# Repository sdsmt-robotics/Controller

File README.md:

# ARCHIVED. USE GITLAB.

# Controller
Repo is used to document all the iterations for the controller

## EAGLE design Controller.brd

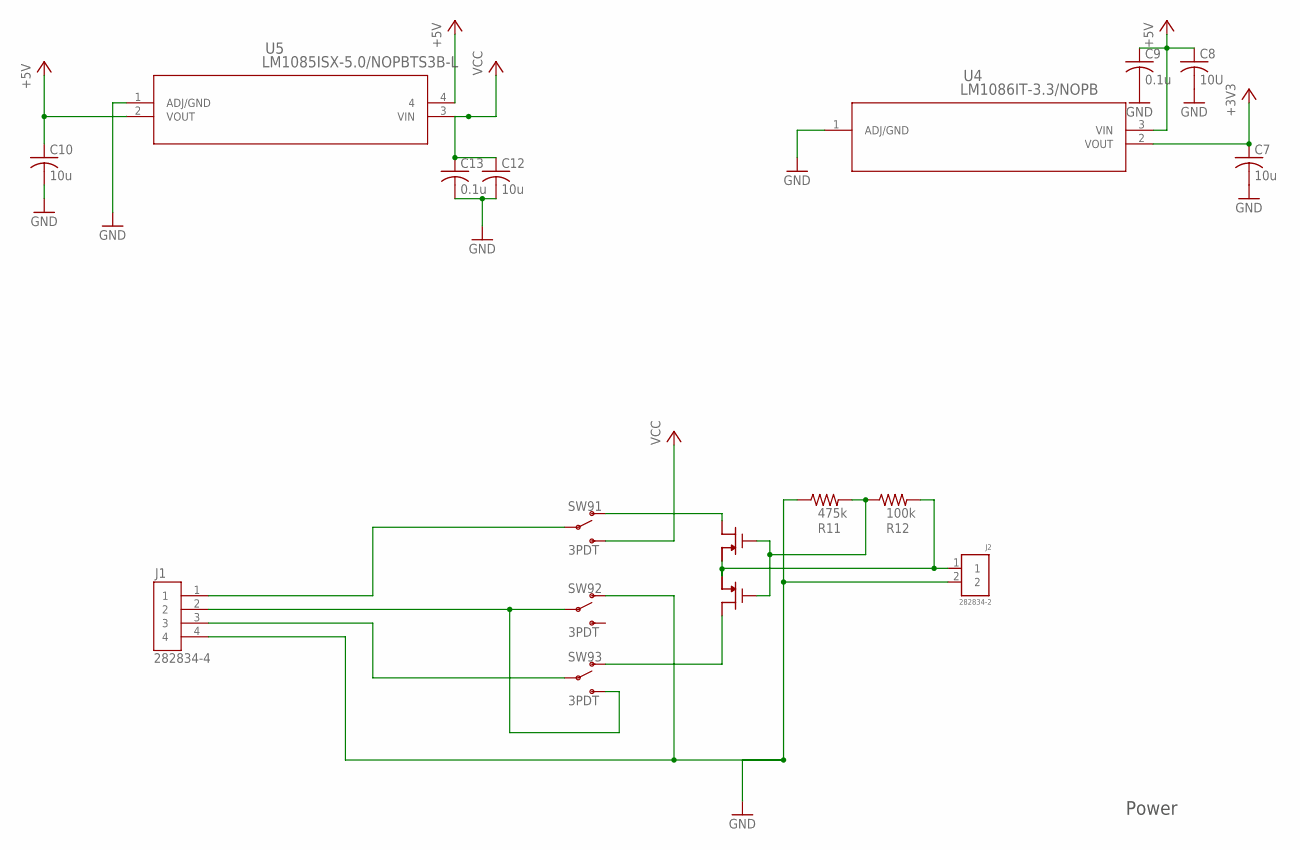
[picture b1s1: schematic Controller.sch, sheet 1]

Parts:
C7, C10, C12: 10u; C1206
C8: 10U; C1206
C9, C13: 0.1u; C1206
J1: 282834-4; HDRV4W85P254_4X1_1062X650X1000
J2: 282834-2; CONN_282834-2
R11: 475k; R1206
R12: 100k; R1206
SW9: 3PDT
U4: LM1086IT-3.3/NOPB; T03B
U5: LM1085ISX-5.0/NOPBTS3B-L; TS3B-L
U6: SSM6P40TULFCT-ND; SMD6

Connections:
+3V3: C7.1, U4.2 (VOUT); also elsewhere on the board
+5V: C8.1, C9.1, C10.1, U4.3 (VIN), U5.2 (VOUT), U5.4; also elsewhere on the board
GND: C7.2, C8.2, C9.2, C10.2, C12.2, C13.2, J1.4, J2.2, R11.1, SW9.T21 (O), U4.1 (ADJ/GND), U5.1 (ADJ/GND); also elsewhere on the board
unnamed: J1.1, SW9.P1
unnamed: J1.2, SW9.P2, SW9.T32 (S)
unnamed: J1.3, SW9.P3
unnamed: SW9.T31 (O), U6.P$3 (D)
unnamed: J2.1, R12.2, U6.P$1 (S), U6.P$4 (S)
unnamed: SW9.T11 (O), U6.P$6 (D)
unnamed: R11.2, R12.1, U6.P$2 (G), U6.P$5 (G)
VCC: C12.1, C13.1, SW9.T12 (S), U5.3 (VIN)

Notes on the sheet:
Power

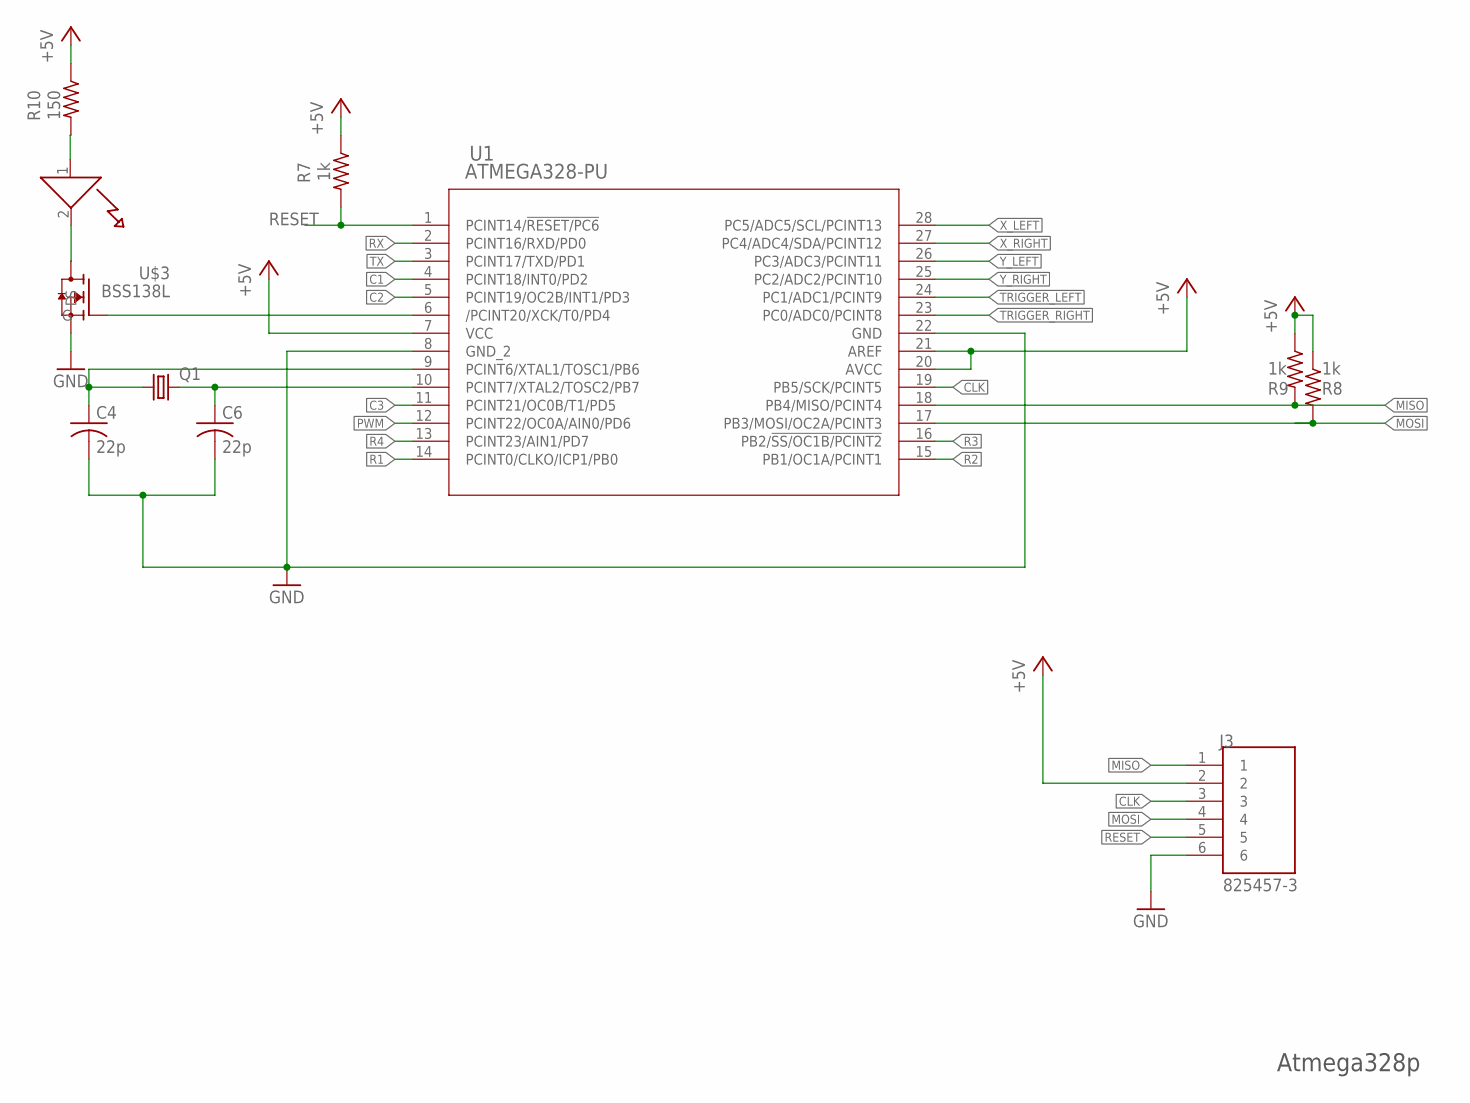
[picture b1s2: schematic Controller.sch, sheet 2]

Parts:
C4, C6: 22p; C1206
J3: 825457-3; TE_825457-3
Q1: CRYSTALHC49S; HC49/S
R7, R8, R9: 1k; R1206
R10: 150; R1206
U1: ATMEGA328-PU; 28P3
U$2: LED; R1206W
U$3: BSS138L

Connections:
+5V: J3.2, R7.1, R8.1, R9.1, R10.1, U1.7 (VCC), U1.20 (AVCC), U1.21 (AREF); also elsewhere on the board
C1: U1.4 (PCINT18/INT0/PD2); also elsewhere on the board
C2: U1.5 (PCINT19/OC2B/INT1/PD3); also elsewhere on the board
C3: U1.11 (PCINT21/OC0B/T1/PD5); also elsewhere on the board
CLK: J3.3, U1.19 (PB5/SCK/PCINT5)
GND: C4.2, C6.2, J3.6, U1.8 (GND_2), U1.22 (GND), U$3.S; also elsewhere on the board
MISO: J3.1, R9.2, U1.18 (PB4/MISO/PCINT4)
MOSI: J3.4, R8.2, U1.17 (PB3/MOSI/OC2A/PCINT3)
unnamed: C4.1, Q1.1, U1.9 (PCINT6/XTAL1/TOSC1/PB6)
unnamed: C6.1, Q1.2, U1.10 (PCINT7/XTAL2/TOSC2/PB7)
unnamed: U1.6 (/PCINT20/XCK/T0/PD4), U$3.G
unnamed: U$2.2, U$3.D
unnamed: R10.2, U$2.1
PWM: U1.12 (PCINT22/OC0A/AIN0/PD6)
R1: U1.14 (PCINT0/CLKO/ICP1/PB0); also elsewhere on the board
R2: U1.15 (PB1/OC1A/PCINT1); also elsewhere on the board
R3: U1.16 (PB2/!SS/OC1B/PCINT2); also elsewhere on the board
R4: U1.13 (PCINT23/AIN1/PD7); also elsewhere on the board
RESET: J3.5, R7.2, U1.1 (PCINT14/!RESET/PC6)
RX: U1.2 (PCINT16/RXD/PD0); also elsewhere on the board
TRIGGER_LEFT: U1.24 (PC1/ADC1/PCINT9); also elsewhere on the board
TRIGGER_RIGHT: U1.23 (PC0/ADC0/PCINT8); also elsewhere on the board
TX: U1.3 (PCINT17/TXD/PD1); also elsewhere on the board
X_LEFT: U1.28 (PC5/ADC5/SCL/PCINT13); also elsewhere on the board
X_RIGHT: U1.27 (PC4/ADC4/SDA/PCINT12); also elsewhere on the board
Y_LEFT: U1.26 (PC3/ADC3/PCINT11); also elsewhere on the board
Y_RIGHT: U1.25 (PC2/ADC2/PCINT10); also elsewhere on the board

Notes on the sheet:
Atmega328p

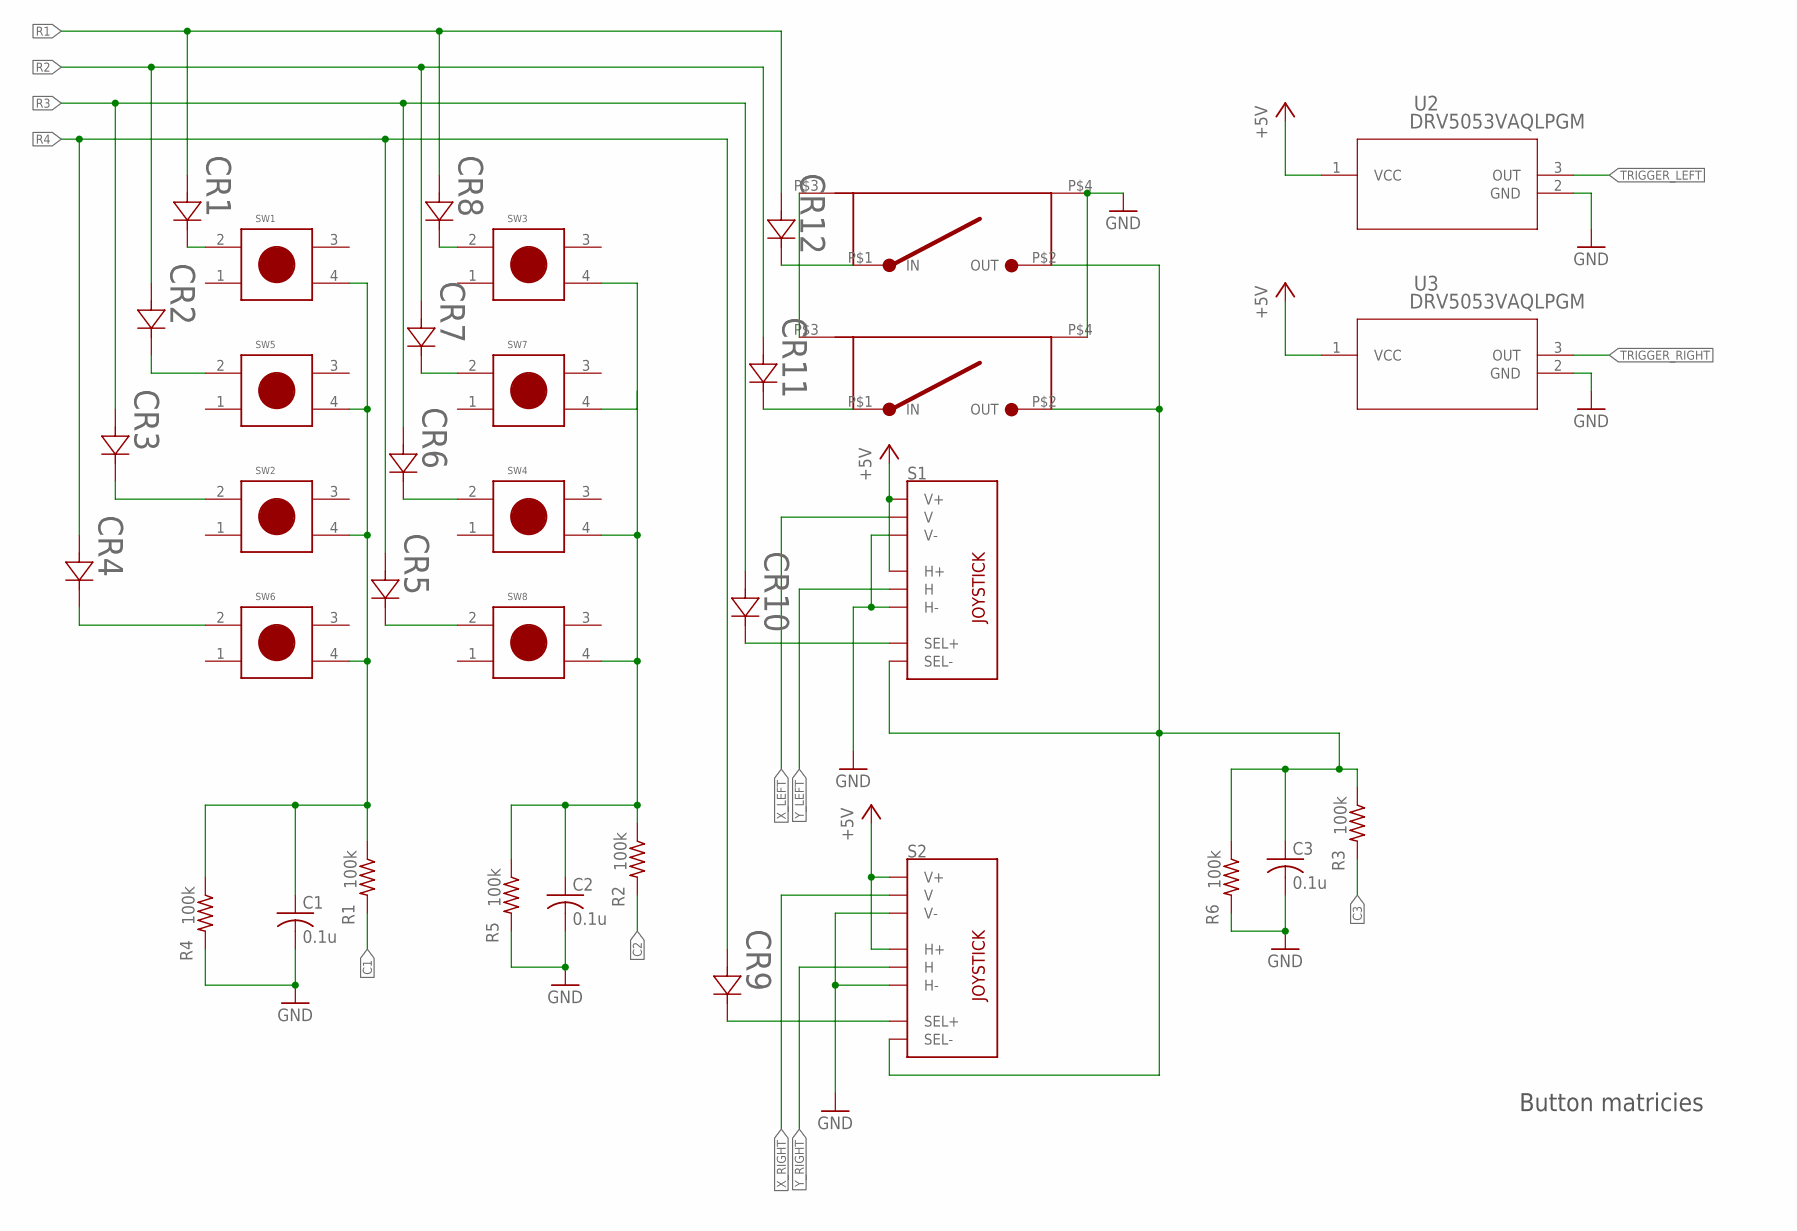
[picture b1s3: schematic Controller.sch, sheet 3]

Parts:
C1, C2, C3: 0.1u; C1206
CR1, CR2, CR3, CR4, CR5, CR6, CR7, CR8, CR9, CR10, CR11, CR12: MSS1P6-M3/89ADIODE_MSP3V3-M; DIODE_MSP3V3-M
R1, R2, R3, R4, R5, R6: 100k; R1206
S1, S2: THUMBPOINTER-RKJXV1224005
SW1, SW2, SW3, SW4, SW5, SW6, SW7, SW8: MULTICOLOR_BUTTON; PRT-14460
U2, U3: DRV5053VAQLPGM; LPG3
U$4, U$6: BUMPER_BUMPER

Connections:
$NC1: C1.1, R1.1, R4.1, SW1.4, SW2.4, SW5.4, SW6.4
+5V: S1.H1 (H+), S1.V1 (V+), S2.H1 (H+), S2.V1 (V+), U2.1 (VCC), U3.1 (VCC); also elsewhere on the board
C1: R1.2; also elsewhere on the board
C2: R2.2; also elsewhere on the board
C3: R3.2; also elsewhere on the board
GND: C1.2, C2.2, C3.2, R4.2, R5.2, R6.2, S1.H3 (H-), S1.V3 (V-), S2.H3 (H-), S2.V3 (V-), U2.2 (GND), U3.2 (GND), U$4.P$4 (GROUND), U$6.P$4 (GROUND); also elsewhere on the board
unnamed: CR4.1, SW6.2
unnamed: U$4.P$3 (GROUND1), U$6.P$3 (GROUND1)
unnamed: CR3.1, SW2.2
unnamed: CR2.1, SW5.2
unnamed: CR1.1, SW1.2
unnamed: CR7.1, SW7.2
unnamed: CR6.1, SW4.2
unnamed: CR5.1, SW8.2
unnamed: CR12.1, U$4.P$1 (IN)
unnamed: CR8.1, SW3.2
unnamed: CR11.1, U$6.P$1 (IN)
unnamed: CR10.1, S1.B1A (SEL+)
unnamed: CR9.1, S2.B1A (SEL+)
N$C2: C2.1, R2.1, R5.1, SW3.4, SW4.4, SW7.4, SW8.4
N$C3: C3.1, R3.1, R6.1, S1.B2A (SEL-), S2.B2A (SEL-), U$4.P$2 (OUT), U$6.P$2 (OUT)
R1: CR1.2, CR8.2, CR12.2; also elsewhere on the board
R2: CR2.2, CR7.2, CR11.2; also elsewhere on the board
R3: CR3.2, CR6.2, CR10.2; also elsewhere on the board
R4: CR4.2, CR5.2, CR9.2; also elsewhere on the board
TRIGGER_LEFT: U2.3 (OUT); also elsewhere on the board
TRIGGER_RIGHT: U3.3 (OUT); also elsewhere on the board
X_LEFT: S1.V2 (V); also elsewhere on the board
X_RIGHT: S2.V2 (V); also elsewhere on the board
Y_LEFT: S1.H2 (H); also elsewhere on the board
Y_RIGHT: S2.H2 (H); also elsewhere on the board

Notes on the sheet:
Button matricies

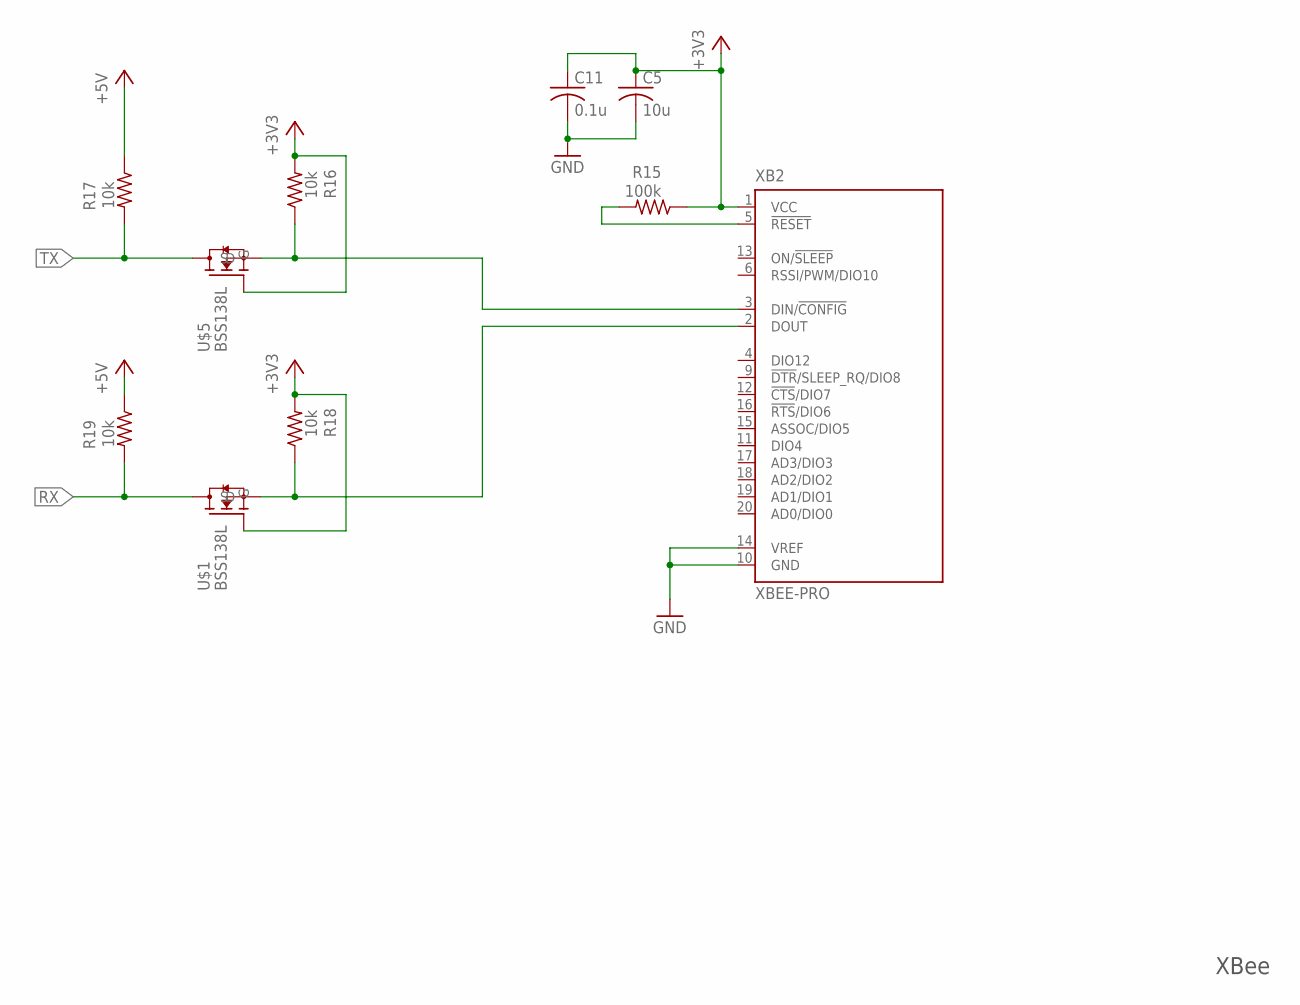
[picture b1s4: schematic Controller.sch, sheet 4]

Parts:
C5: 10u; C1206
C11: 0.1u; C1206
R15: 100k; R1206
R16, R17, R18, R19: 10k; R1206
U$1, U$5: BSS138L
XB2: XBEE-PRO

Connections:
+3V3: C5.1, C11.1, R15.1, R16.2, R18.2, U$1.G, U$5.G, XB2.1 (VCC); also elsewhere on the board
+5V: R17.1, R19.1; also elsewhere on the board
GND: C5.2, C11.2, XB2.10 (GND), XB2.14 (VREF); also elsewhere on the board
unnamed: R15.2, XB2.5 (!RESET)
unnamed: R16.1, U$5.S, XB2.3 (DIN/!CONFIG)
unnamed: R18.1, U$1.S, XB2.2 (DOUT)
RX: R19.2, U$1.D; also elsewhere on the board
TX: R17.2, U$5.D; also elsewhere on the board

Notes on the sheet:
XBee

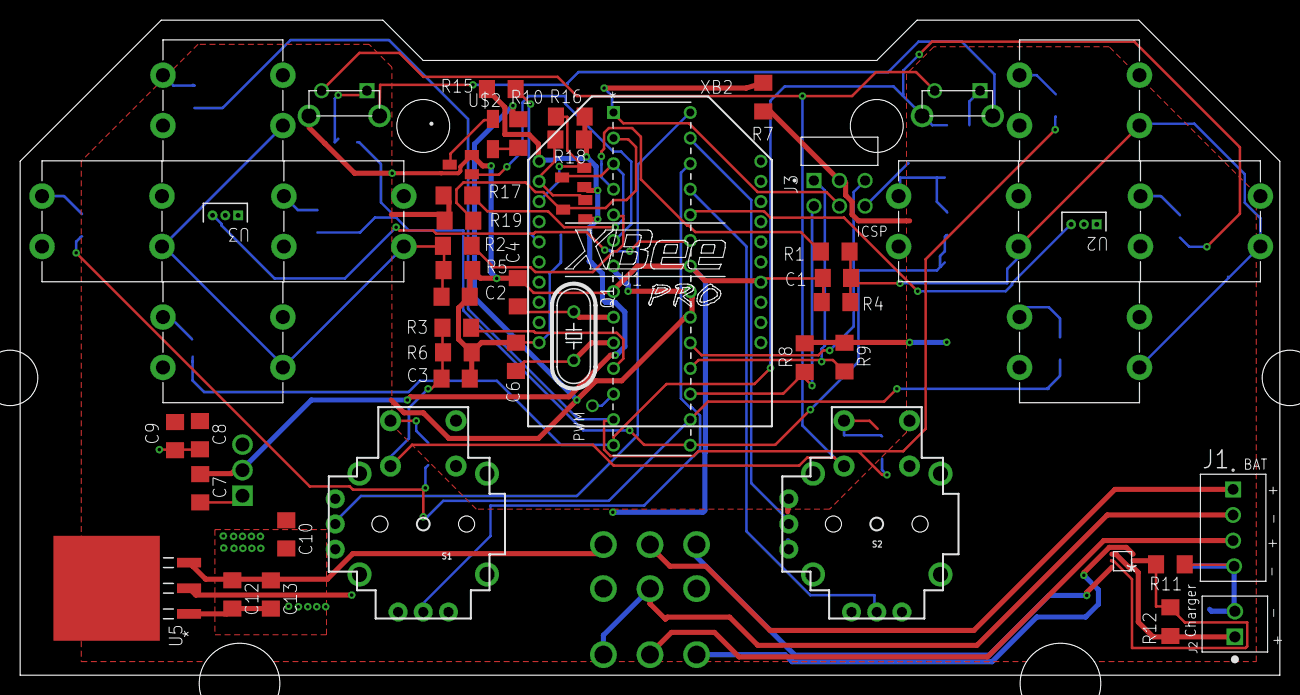
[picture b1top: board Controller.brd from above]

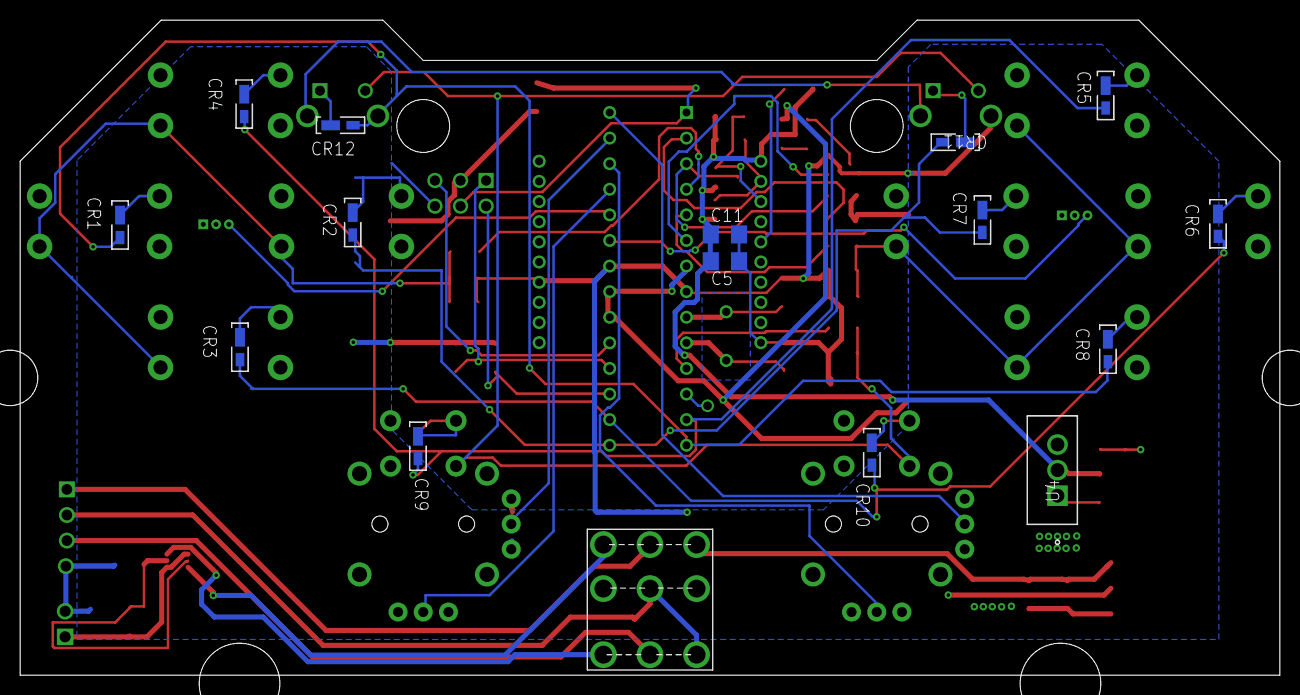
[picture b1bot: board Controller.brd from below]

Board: 2 copper layers, 125.0 x 65.0 mm, 70 parts (16 on the bottom side), 54 nets.

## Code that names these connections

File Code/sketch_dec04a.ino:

void setup() {
  // put your setup code here, to run once:
  DDRD |= (1<<PD2)|(1<<PD3)|(1<<PD4)|(1<<PD5)|(1<<PD7); // Set pins as output
  DDRB |= (1<<PB0)|(1<<PB1)|(PB2); // Set pins as output

  Serial.begin(9600);

}

void loop() {
  // put your main code here, to run repeatedly

  PORTD |= (1<<PD4); // Turn on LED
  
  while(1) // Redundant loop to by-pass Arduino overhead and increase runtime
  {
    uint16_t message_frame[10]={};
    char row_flag = 0x00; //Setup flags for what row is currently being toggled
    uint16_t *col_flag = 0x01; // and what col button might be pressed

    setframe(message_frame,row_flag++,*col_flag);
    
   // "x" in the following comments is the effective Arduino pin that's mapped to appropriate pin 
   // on the chip. Lookup Arduino pinout : https://www.circuito.io/blog/arduino-uno-pinout/
   // Notice in the picture how pin 6 on the chip is actually digital pin 4 on the arduino and is BIT
   // 4 in the D register (PD4)

  
   
    PORTB |= (1<<PB0); // digitalWrite(x,HIGH) -> Use PORTX when writing to registers, PINX when reading and DDRX when setting the pinMode
    col_flag = CheckKeyPress(); // Check for key presses
    PORTB &= ~(1<<PB0); // digitalWrite(x,LOW)
    setframe(message_frame,row_flag++,*col_flag);

    
    PORTB |= (1<<PB1);
    col_flag = CheckKeyPress();
    PORTB &= ~(1<<PB1);
    setframe(message_frame,row_flag++,*col_flag);

    PORTB |= (1<<PB2);
    col_flag = CheckKeyPress();
    PORTB &= ~(1<<PB2);
    setframe(message_frame,row_flag++,*col_flag);


    PORTD |= (1<<PD7);
    col_flag = CheckKeyPress();
    PORTB &= ~(1<<PD7);  
    setframe(message_frame,row_flag++,*col_flag);

    
    col_flag = analogRead(A0);
    setframe(message_frame,row_flag++,*col_flag);


    col_flag = analogRead(A1);
    setframe(message_frame,row_flag++,*col_flag);

    col_flag = analogRead(A2);
    setframe(message_frame,row_flag++,*col_flag);

    col_flag = analogRead(A3);
    setframe(message_frame,row_flag++,*col_flag);

    col_flag = analogRead(A4);
    setframe(message_frame,row_flag++,*col_flag);


    col_flag = analogRead(A5);
    setframe(message_frame,row_flag++,*col_flag);

    col_flag = 0x04;
    setframe(message_frame,row_flag,*col_flag);

    sendframe(message_frame);
 
  }
}

char CheckKeyPress(){
  char dreg = PIND; // Read the whole input register -> registers are 8 bit. No point in using int (32 bits). Can also use uint_8t
  if(dreg & (1<<PD2)) // If the PD2 bit in the register is set, return 1
    return 0x01;
  if(dreg & (1<<PD3))
    return 0x02;
  if(dreg & (1<<PD5))
    return 0x03;
} 

void setframe(uint16_t frame[], char index, uint16_t &col_flag)
{
    frame[index] = (col_flag);  

    col_flag = 0x00; 
}

void sendframe(uint16_t message_frame[])
{
  char i=0;
  do
  {
    Serial.write(message_frame[i]);
    delay(10);                            //UART is quirky. Can't be sending stuff too fast.
    Serial.write(message_frame[i]>>8); 
    delay(10);

  }
  while(message_frame[i++] != 0x04);

}

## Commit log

2019-09-14 Added buttons and a switch
2019-09-15 Redid debounce filter and added unity gain buffer. Added Xbee and logic level shifter for RX and TX
2019-09-15 Added 16MHz oscillator for Atmega328p
2019-09-15 Fixed connection error in Low Pass filter
2019-10-05 Update Controller.lbr
    Made a couple of changes to the board outline. Add zeners to the each button
2019-10-11 Added more holes, did some routing added 3D models
2019-10-11 MORE ROUTING!!
2019-10-12 Routing
    Routed most of the board. Need to add power components and Zeners
2019-10-19 Changes
    Added more 3D models. Changed to a ATMega2560
2019-10-20 Added Charlieplexed button matrix
    Will now have to turn on PORTB bits 1:3
2019-10-20 Added Hall effect sensors
2019-10-21 Redoing the board
2019-10-24 Added Board
2019-10-24 added 5V regulator
    Still need to add BMS circuitry and switch
2019-10-28 rerouted so we only have 2 layers, added PWM pin
    Need to add battery switch,indicator Vbat pins
2019-11-01 Added switch and LED
2019-11-02 finished?
2019-11-02 Added a License
2019-11-02 Added coherent BOM
2019-11-03 Added diodes and made traces 10 mills
2019-11-03 Minor Changes and added Gerber
2019-11-04 Updated trace width for power
    All Power traces (VCC, +3V3 and 5V) are rated for 1.5A. All other traces are rated for 0.8A
2019-11-04 Added Gerbers
2019-11-04 Added Sam's holes
2019-11-04 Read Desc.
    * Moved Bumpers 3mm lower
    * changed TO diodes to SMD
    * Chnaged BOM to shorter actuator buttons
2019-11-21 Fixed overlap and deleted some stubs
2019-12-09 Finished code? Needs to be tested
2020-01-13 Fixed pin toggeling
    Had to NOT some bits to set the pin LOW
2020-01-18 Tested
2020-02-02 Update sketch_dec04a.ino
    Mostly working controller code. Still have to fix recieving more than one button press when only pressed once. Must also make sure hall effect sensors work.
2020-02-29 Debounced buttons
    Hopefully, it's done and I don't need to adjust any delays
2020-03-01 FIxed
    Have Sam check
2020-03-13 Fix formatting in README
2020-03-13 Add communications code and documentation
2020-03-14 Fix missing joystick button in receive demo code
2020-03-14 Add code for rev3 of the controller
2020-03-15 Improve data transmission and add some functions to clean up analog values
    * Increased xbee baudrate to 115200. Nothing has caught on fire yet...
    * Split full sends into two halves so we are less likely to overflow the serial buffer.
    * Added a joystick deadzone function to the receive code
    * Changed over to floats for analog values. Performance doesn't take that much of a hit, and it is much more usable.
    * Added some scaling to analog values for rev3.
    * Added some documentation for the rev3 code.
2020-03-16 Add (mostly) working rev2 code
2020-03-17 Update documentation to add rev2 notes
2020-03-17 Add button debouncing to rev2 code
2020-08-26 Add changes to example receive code
2020-12-31 Remove debugging stuff
2022-06-14 Addimg readme
2022-06-14 Updating README
2022-06-14 Test commit
2022-08-19 Adding new block diagram
2022-08-28 Updating Files
2022-08-28 Adding CubeMX config file and generated code
2022-08-31 Updating for 3v3 operation
2022-08-31 Adding power dissipation notes. Removing WS2821B since they won't work with a 3v3 supply
2022-08-31 updating label directions
2022-09-01 Added buzz and vibe, moved SPI, added 2 LEDs
2022-09-01 Updating sheet template
2022-09-01 added switch
2022-09-02 Added Xbee libs and bus aliases
2022-09-02 Updating title block fields and adding pdf schematic
2022-09-02 Adding Block svg
2022-09-07 Adding pull ups on I2C lines
2022-09-25 Fixing USB pins and added SPI_CS
2022-09-25 Adding some device footprints and MPN
2022-10-15 No clue what changed
2022-10-21 Removed unnecessary FETs
2022-11-25 Adding footprints
2022-12-03 fix relative path for template
2022-12-03 archive
